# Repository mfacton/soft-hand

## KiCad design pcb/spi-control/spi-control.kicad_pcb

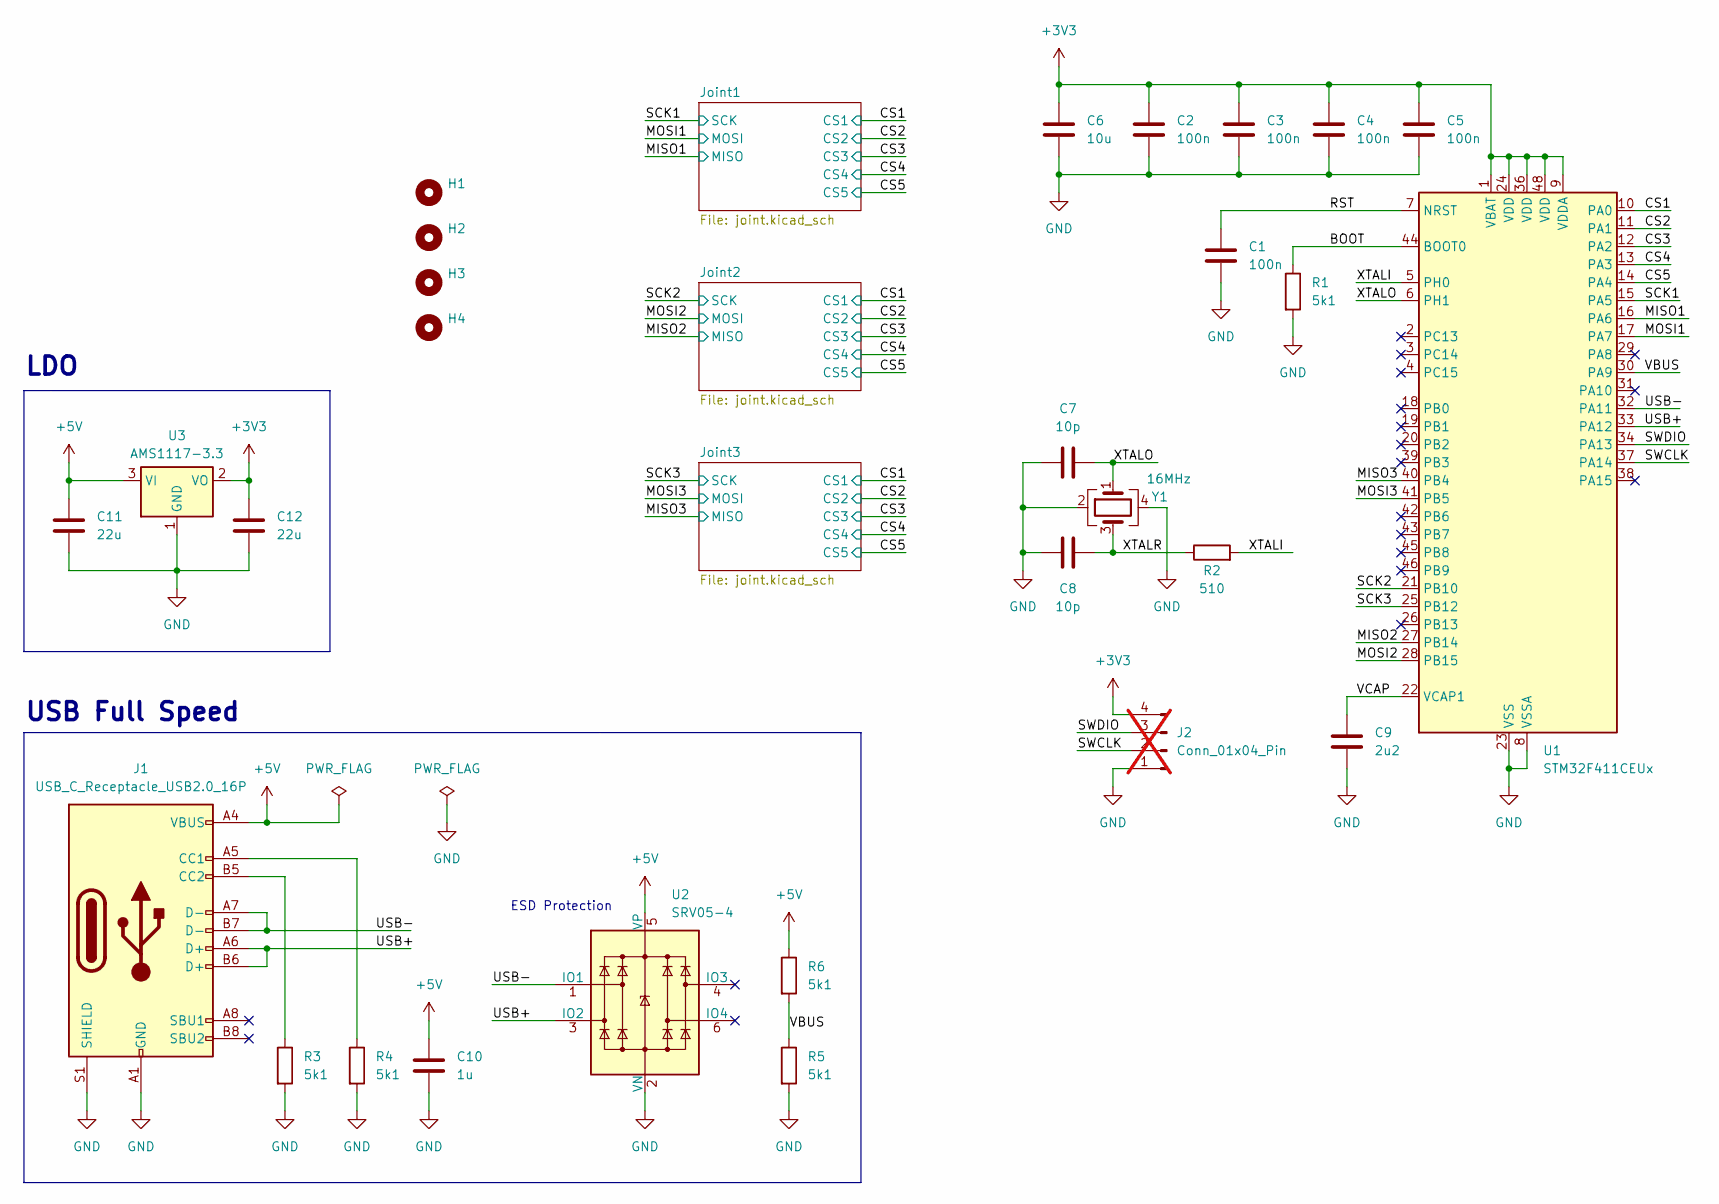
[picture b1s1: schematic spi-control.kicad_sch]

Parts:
C1, C2, C3, C4, C5: 100n; C_0402_1005Metric; LCSC C1525
C6: 10u; C_0402_1005Metric; LCSC C15525
C7, C8: 10p; C_0402_1005Metric; LCSC C32949
C9: 2u2; C_0402_1005Metric; LCSC C12530
C10: 1u; C_0402_1005Metric; LCSC C52923
C11: 22u; C_0805_2012Metric; LCSC C45783
C12: 22u; C_0603_1608Metric; LCSC C59461
H1, H2, H3, H4: MountingHole; MountingHole_2.5mm
J1: USB_C_Receptacle_USB2.0_16P; USB_C_Receptacle_GCT_USB4105-xx-A_16P_TopMnt_Horizontal; LCSC C2765186
J2: Conn_01x04_Pin; PinHeader_1x04_P2.54mm_Vertical; not fitted
R1, R3, R4, R5, R6: 5k1; R_0402_1005Metric; LCSC C25905
R2: 510; R_0402_1005Metric; LCSC C25123
U1: STM32F411CEUx; QFN-48-1EP_7x7mm_P0.5mm_EP5.6x5.6mm; LCSC C60420
U2: SRV05-4; SOT-23-6; LCSC C7420376
U3: AMS1117-3.3; SOT-223-3_TabPin2; LCSC C6186
Y1: 16MHz; Crystal_SMD_3225-4Pin_3.2x2.5mm; LCSC C13738

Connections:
+3V3: C2.1, C3.1, C4.1, C5.1, C6.1, C12.1, J2.4, U1.1 (VBAT), U1.9 (VDDA), U1.24 (VDD), U1.36 (VDD), U1.48 (VDD), U3.2 (VO); also elsewhere on the board
+5V: C10.1, C11.1, J1.A4 (VBUS), J1.A9 (VBUS), J1.B4 (VBUS), J1.B9 (VBUS), R6.1, U2.5 (VP), U3.3 (VI)
/BOOT: R1.1, U1.44 (BOOT0)
/CS1: U1.10 (PA0); also elsewhere on the board
/CS2: U1.11 (PA1); also elsewhere on the board
/CS3: U1.12 (PA2); also elsewhere on the board
/CS4: U1.13 (PA3); also elsewhere on the board
/CS5: U1.14 (PA4); also elsewhere on the board
/MISO1: U1.16 (PA6); also elsewhere on the board
/MISO2: U1.27 (PB14); also elsewhere on the board
/MISO3: U1.40 (PB4); also elsewhere on the board
/MOSI1: U1.17 (PA7); also elsewhere on the board
/MOSI2: U1.28 (PB15); also elsewhere on the board
/MOSI3: U1.41 (PB5); also elsewhere on the board
/RST: C1.1, U1.7 (NRST)
/SCK1: U1.15 (PA5); also elsewhere on the board
/SCK2: U1.21 (PB10); also elsewhere on the board
/SCK3: U1.25 (PB12); also elsewhere on the board
/SWCLK: J2.2, U1.37 (PA14)
/SWDIO: J2.3, U1.34 (PA13)
/USB+: J1.A6 (D+), J1.B6 (D+), U1.33 (PA12), U2.3 (IO2)
/USB-: J1.A7 (D-), J1.B7 (D-), U1.32 (PA11), U2.1 (IO1)
/VBUS: R5.1, R6.2, U1.30 (PA9)
/VCAP: C9.1, U1.22 (VCAP1)
/XTALI: R2.2, U1.5 (PH0)
/XTALO: C7.2, U1.6 (PH1), Y1.1
/XTALR: C8.2, R2.1, Y1.3
GND: C1.2, C2.2, C3.2, C4.2, C5.2, C6.2, C7.1, C8.1, C9.2, C10.2, C11.2, C12.2, J1.A1 (GND), J1.A12 (GND), J1.B1 (GND), J1.B12 (GND), J1.S1 (SHIELD), J2.1, R1.2, R3.2, R4.2, R5.2, U1.8 (VSSA), U1.23 (VSS), U1.35 (VSS), U1.47 (VSS), U1.49 (VSS), U2.2 (VN), U3.1 (GND), Y1.2, Y1.4; also elsewhere on the board
unnamed: J1.A5 (CC1), R4.1
unnamed: J1.B5 (CC2), R3.1

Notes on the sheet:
USB Full Speed
LDO
ESD Protection

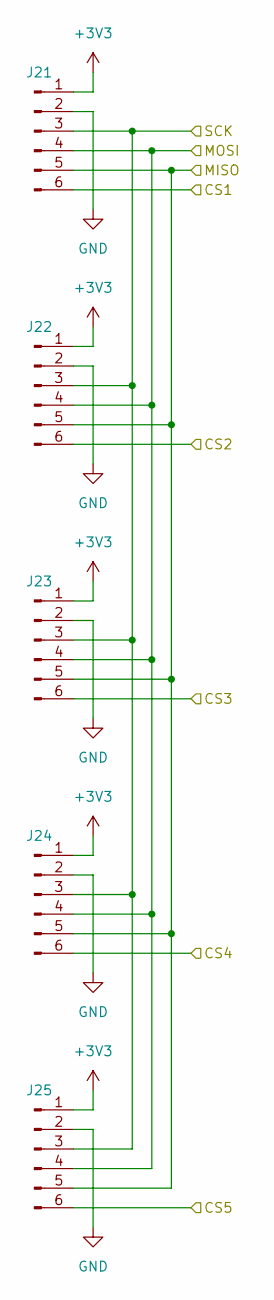
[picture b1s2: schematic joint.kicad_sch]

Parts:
J21, J22, J23, J24, J25: Conn_01x06_Pin; TerminalBlock_Phoenix_MPT-0,5-6-2.54_1x06_P2.54mm_Horizontal; LCSC C5188446

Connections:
+3V3: J21.1, J22.1, J23.1, J24.1, J25.1; also elsewhere on the board
/CS1: J21.6; also elsewhere on the board
/CS2: J22.6; also elsewhere on the board
/CS3: J23.6; also elsewhere on the board
/CS4: J24.6; also elsewhere on the board
/CS5: J25.6; also elsewhere on the board
/MISO2: J21.5, J22.5, J23.5, J24.5, J25.5; also elsewhere on the board
/MOSI2: J21.4, J22.4, J23.4, J24.4, J25.4; also elsewhere on the board
/SCK2: J21.3, J22.3, J23.3, J24.3, J25.3; also elsewhere on the board
GND: J21.2, J22.2, J23.2, J24.2, J25.2; also elsewhere on the board

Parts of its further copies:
J16, J17, J18, J19, J20, J26, J27, J28, J29, J30: Conn_01x06_Pin; TerminalBlock_Phoenix_MPT-0,5-6-2.54_1x06_P2.54mm_Horizontal; LCSC C5188446

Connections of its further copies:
+3V3: J16.1, J17.1, J18.1, J19.1, J20.1, J26.1, J27.1, J28.1, J29.1, J30.1; also elsewhere on the board
/CS1: J16.6, J26.6; also elsewhere on the board
/CS2: J17.6, J27.6; also elsewhere on the board
/CS3: J18.6, J28.6; also elsewhere on the board
/CS4: J19.6, J29.6; also elsewhere on the board
/CS5: J20.6, J30.6; also elsewhere on the board
/MISO1: J16.5, J17.5, J18.5, J19.5, J20.5; also elsewhere on the board
/MISO3: J26.5, J27.5, J28.5, J29.5, J30.5; also elsewhere on the board
/MOSI1: J16.4, J17.4, J18.4, J19.4, J20.4; also elsewhere on the board
/MOSI3: J26.4, J27.4, J28.4, J29.4, J30.4; also elsewhere on the board
/SCK1: J16.3, J17.3, J18.3, J19.3, J20.3; also elsewhere on the board
/SCK3: J26.3, J27.3, J28.3, J29.3, J30.3; also elsewhere on the board
GND: J16.2, J17.2, J18.2, J19.2, J20.2, J26.2, J27.2, J28.2, J29.2, J30.2; also elsewhere on the board

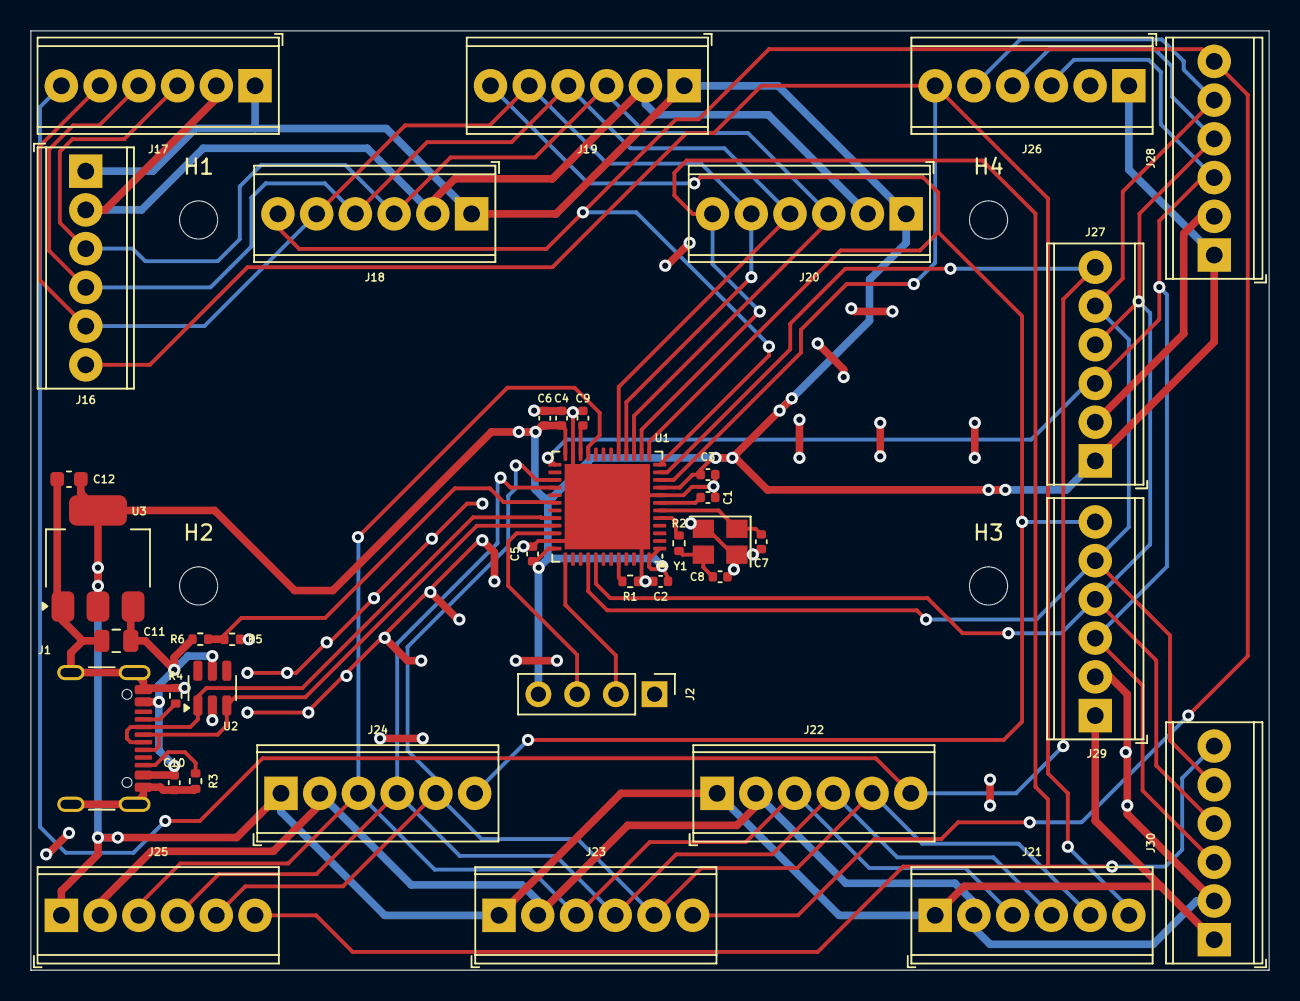
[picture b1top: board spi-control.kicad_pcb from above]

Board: 2 copper layers, 81.2 x 61.6 mm, 43 parts (0 on the bottom side), 30 nets.

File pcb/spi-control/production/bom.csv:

Designator,Footprint,Quantity,Value,LCSC Part #
"C1, C2, C3, C4, C5",0402,5,100n,C1525
C10,0402,1,1u,C52923
C11,0805,1,22u,C45783
C12,0603,1,22u,C59461
C6,0402,1,10u,C15525
"C7, C8",0402,2,10p,C32949
C9,0402,1,2u2,C12530
J1,USB_C_Receptacle_GCT_USB4105-xx-A_16P_TopMnt_Horizontal,1,USB_C_Receptacle_USB2.0_16P,C2765186
"J16, J17, J18, J19, J20, J21, J22, J23, J24, J25, J26, J27, J28, J29, J30","TerminalBlock_Phoenix_MPT-0,5-6-2.54_1x06_P2.54mm_Horizontal",15,Conn_01x06_Pin,C5188446
"R1, R3, R4, R5, R6",0402,5,5k1,C25905
R2,0402,1,510,C25123
U1,QFN-48-1EP_7x7mm_P0.5mm_EP5.6x5.6mm,1,STM32F411CEUx,C60420
U2,SOT-23-6,1,SRV05-4,C7420376
U3,SOT-223-3_TabPin2,1,AMS1117-3.3,C6186
Y1,Crystal_SMD_3225-4Pin_3.2x2.5mm,1,16MHz,C13738

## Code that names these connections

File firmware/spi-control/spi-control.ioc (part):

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Mcu.Name=STM32F411C(C-E)Ux
Mcu.Package=UFQFPN48
Mcu.UserName=STM32F411CEUx
PA0-WKUP.GPIOParameters=PinState,GPIO_Label
PA0-WKUP.GPIO_Label=CS1
PA0-WKUP.PinState=GPIO_PIN_SET
PA0-WKUP.Signal=GPIO_Output
PA1.GPIOParameters=PinState,GPIO_Label
PA1.GPIO_Label=CS2
PA1.PinState=GPIO_PIN_SET
PA1.Signal=GPIO_Output
PA11.Mode=Device_Only
PA11.Signal=USB_OTG_FS_DM
PA12.Mode=Device_Only
PA12.Signal=USB_OTG_FS_DP
PA13.Mode=Serial_Wire
PA13.Signal=SYS_JTMS-SWDIO
PA14.Mode=Serial_Wire
PA14.Signal=SYS_JTCK-SWCLK
PA2.GPIOParameters=PinState,GPIO_Label
PA2.GPIO_Label=CS3
PA2.PinState=GPIO_PIN_SET
PA2.Signal=GPIO_Output
PA3.GPIOParameters=PinState,GPIO_Label
PA3.GPIO_Label=CS4
PA3.PinState=GPIO_PIN_SET
PA3.Signal=GPIO_Output
PA4.GPIOParameters=PinState,GPIO_Label
PA4.GPIO_Label=CS5
PA4.PinState=GPIO_PIN_SET
PA4.Signal=GPIO_Output
PA5.Mode=Full_Duplex_Master
PA5.Signal=SPI1_SCK
PA6.Mode=Full_Duplex_Master
PA6.Signal=SPI1_MISO
PA7.Mode=Full_Duplex_Master
PA7.Signal=SPI1_MOSI
PB10.Mode=Full_Duplex_Master
PB10.Signal=SPI2_SCK
PB12.Mode=Full_Duplex_Master
PB12.Signal=SPI3_SCK
PB14.Mode=Full_Duplex_Master
PB14.Signal=SPI2_MISO
PB15.Mode=Full_Duplex_Master
PB15.Signal=SPI2_MOSI
PB4.Mode=Full_Duplex_Master
PB4.Signal=SPI3_MISO
PB5.Mode=Full_Duplex_Master
PB5.Signal=SPI3_MOSI
PH0\ -\ OSC_IN.Mode=HSE-External-Oscillator
PH0\ -\ OSC_IN.Signal=RCC_OSC_IN
PH1\ -\ OSC_OUT.Mode=HSE-External-Oscillator
PH1\ -\ OSC_OUT.Signal=RCC_OSC_OUT
RCC.HSE_VALUE=16000000
RCC.SYSCLKFreq_VALUE=96000000
RCC.SYSCLKSource=RCC_SYSCLKSOURCE_PLLCLK
board=custom

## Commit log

2024-09-05 Finish schematic and component layout
2024-09-06 Finish pcb design
2024-09-23 Finish firmware
2024-09-23 Add ros node and tester
2024-09-26 Add img refrences
